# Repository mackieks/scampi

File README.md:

<picture> <source media="(prefers-color-scheme: dark)" srcset="images/logo.png">  </picture> 

Scampi is a truly universal OSHW audio amp for portablizers. Hardware design is tested and working. Firmware is nearly complete.

Features:

- Low-cost 20x20mm 2-layer PCB
- TLV320AIC3110 codec with stereo 1.3W Class-D amps and Class-AB headphone driver
- 5V-tolerant level-shifted I2S input + analog input
- Onboard switching 3.5mm headphone jack
- Solder jumpers for mode selection (15 modes planned)
- Shrimp-themed!🦐

Recommended speakers: [Nintendo Switch 2 speakers](https://www.aliexpress.us/item/3256809887996046.html)

Headphone jack (remove pegs with flush cutters): [PJ320D](https://www.aliexpress.us/item/3256808202284065.html)

Hardware tested and working! Firmware is nearly complete! Supported modes so far:

- [x] Analog input
- [x] SNES
- [x] N64
- [x] GameCube
- [x] Wii
- [x] Wii U
- [ ] PS1
- [ ] PS2
- [ ] PS3
- [x] Saturn
- [x] Dreamcast
- [ ] XBOX
- [ ] Xbox 360
- [ ] Jaguar
- [ ] Neo Geo

## License
Solderpad Hardware License v2.1

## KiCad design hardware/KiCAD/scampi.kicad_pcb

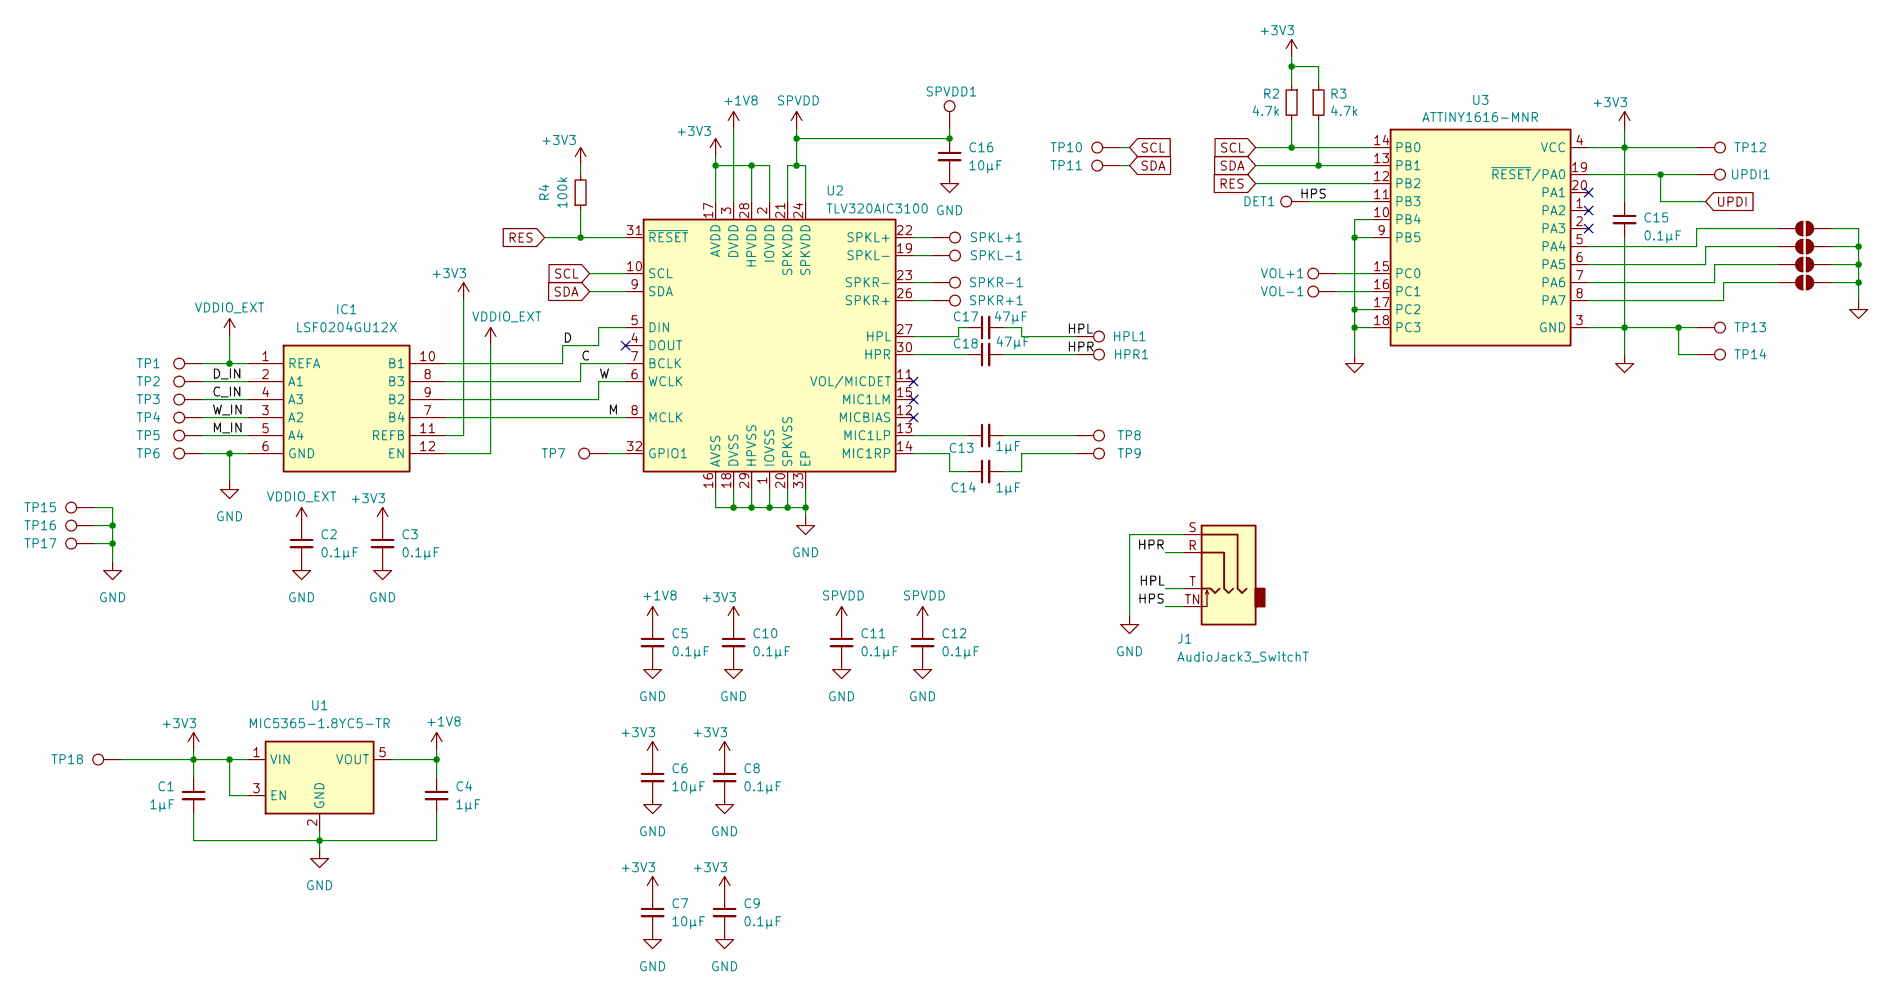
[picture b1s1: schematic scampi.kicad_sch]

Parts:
C1, C4, C13, C14: 1µF; C_0402_1005Metric
C2, C3, C5, C8, C9, C10, C11, C12, C15: 0.1µF; C_0402_1005Metric
C6, C7, C16: 10µF; C_0603_1608Metric
C17, C18: 47µF; C_0603_1608Metric
DET1: pth_pad
HPL1: pth_pad
HPR1: pth_pad
IC1: LSF0204GU12X; Mouser Part Number 771-LSF0204GU12X
J1: AudioJack3_SwitchT; Jack_3.5mm_CUI_SJ-3524-SMT_Horizontal
JP1, JP2, JP3, JP4: SolderJumper_2_Open; small_solder_jumper
R2, R3: 4.7k; R_0402_1005Metric
R4: 100k; R_0402_1005Metric
SPKL+1: pth_pad
SPKL-1: pth_pad
SPKR+1: pth_pad
SPKR-1: pth_pad
SPVDD1: pth_pad
TP1, TP2, TP3, TP4, TP5, TP6, TP8, TP9, TP15, TP16, TP17, TP18: pth_pad
TP7: TestPoint_Pad_D1.0mm
TP10: SCL; TestPoint_Pad_D1.0mm
TP11: SDA; TestPoint_Pad_D1.0mm
TP12: V+; TestPoint_Pad_D1.0mm
TP13: GND; pth_pad
TP14: GND; TestPoint_Pad_D1.0mm
U1: MIC5365-1.8YC5-TR; SOT-353_SC-70-5
U2: TLV320AIC3100; VQFN-32-1EP_5x5mm_P0.5mm_EP3.5x3.5mm
U3: ATTINY1616-MNR; VQFN-20-1EP_3x3mm_P0.4mm_EP1.7x1.7mm
UPDI1: UPDI; TestPoint_Pad_D1.0mm
VOL+1: pth_pad
VOL-1: pth_pad

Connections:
+1V8: C4.1, C5.1, U1.5 (VOUT), U2.3 (DVDD)
+3V3: C1.1, C3.1, C6.1, C7.1, C8.1, C9.1, C10.1, C15.1, IC1.11 (REFB), R2.1, R3.1, R4.2, TP12.1, TP18.1, U1.1 (VIN), U1.3 (EN), U2.2 (IOVDD), U2.17 (AVDD), U2.28 (HPVDD), U3.4 (VCC)
/C: IC1.8 (B3), U2.7 (BCLK)
/C_IN: IC1.4 (A3), TP3.1
/D: IC1.10 (B1), U2.5 (DIN)
/D_IN: IC1.2 (A1), TP2.1
/HPL: C17.2, HPL1.1, J1.T
/HPR: C18.2, HPR1.1, J1.R
/HPS: DET1.1, J1.TN, U3.11 (PB3)
/M: IC1.7 (B4), U2.8 (MCLK)
/M_IN: IC1.5 (A4), TP5.1
/W: IC1.9 (B2), U2.6 (WCLK)
/W_IN: IC1.3 (A2), TP4.1
GND: C1.2, C2.2, C3.2, C4.2, C5.2, C6.2, C7.2, C8.2, C9.2, C10.2, C11.2, C12.2, C15.2, C16.2, IC1.6 (GND), J1.S, JP1.1 (A), JP2.1 (A), JP3.1 (A), JP4.1 (A), TP6.1, TP13.1, TP14.1, TP15.1, TP16.1, TP17.1, U1.2 (GND), U2.1 (IOVSS), U2.16 (AVSS), U2.18 (DVSS), U2.20 (SPKVSS), U2.25 (SPKVSS), U2.29 (HPVSS), U2.33 (EP), U3.3 (GND), U3.9 (PB5), U3.10 (PB4), U3.17 (PC2), U3.18 (PC3), U3.21 (GND)
unnamed: C13.2, TP8.1
unnamed: C14.2, TP9.1
unnamed: JP1.2 (B), U3.5 (PA4)
unnamed: JP2.2 (B), U3.6 (PA5)
unnamed: JP3.2 (B), U3.7 (PA6)
unnamed: JP4.2 (B), U3.8 (PA7)
unnamed: TP7.1, U2.32 (GPIO1)
unnamed: C17.1, U2.27 (HPL)
unnamed: C18.1, U2.30 (HPR)
unnamed: C13.1, U2.13 (MIC1LP)
unnamed: C14.1, U2.14 (MIC1RP)
unnamed: SPKL+1.1, U2.22 (SPKL+)
unnamed: SPKL-1.1, U2.19 (SPKL-)
unnamed: SPKR+1.1, U2.26 (SPKR+)
unnamed: SPKR-1.1, U2.23 (SPKR-)
unnamed: U3.15 (PC0), VOL+1.1
unnamed: U3.16 (PC1), VOL-1.1
RES: R4.1, U2.31 (~RESET), U3.12 (PB2)
SCL: R2.2, TP10.1, U2.10 (SCL), U3.14 (PB0)
SDA: R3.2, TP11.1, U2.9 (SDA), U3.13 (PB1)
SPVDD: C11.1, C12.1, C16.1, SPVDD1.1, U2.21 (SPKVDD), U2.24 (SPKVDD)
UPDI: U3.19 (~RESET/PA0), UPDI1.1
VDDIO_EXT: C2.1, IC1.1 (REFA), IC1.12 (EN), TP1.1

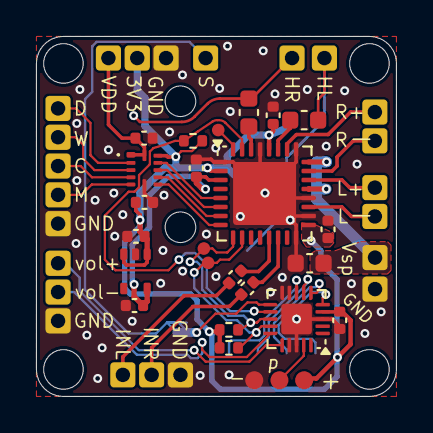
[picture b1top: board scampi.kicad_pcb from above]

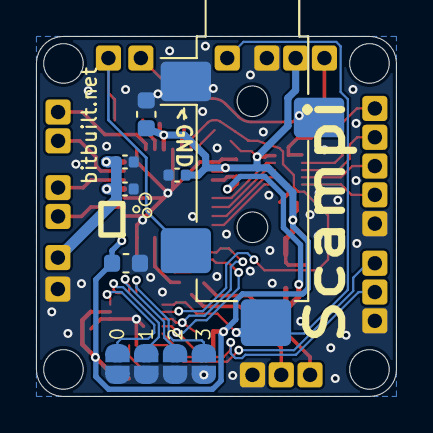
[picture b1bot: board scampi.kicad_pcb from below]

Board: 2 copper layers, 20.0 x 20.0 mm, 59 parts (10 on the bottom side), 37 nets.

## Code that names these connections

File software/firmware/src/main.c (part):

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static volatile uint8_t vol_pot = 0; // analog volume pot reading (0 - 255)

// GPIO pin definitions
static const gpio_t RESET  = {&PORTB, 2}; // PB2
static const gpio_t VOL_UP = {&PORTC, 1}; // PC1
static const gpio_t VOL_DN = {&PORTC, 0}; // PC0
static const gpio_t A_MODE = {&PORTC, 2}; // PC2 (analog vol ctrl mode)

static const gpio_t MODE0 = {&PORTA, 4}; // PA4
static const gpio_t MODE1 = {&PORTA, 5}; // PA5
static const gpio_t MODE2 = {&PORTA, 6}; // PA6
static const gpio_t MODE3 = {&PORTA, 7}; // PA7

// Initialize the RTC for periodic interrupts
void rtc_init()
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
    analog_vol_ctrl = true;

    // ADC1 on VOL_DN (PC0)
    ADC1.CTRLA   = 0x07; // enable ADC in free-running 8-bit mode
    ADC1.CTRLC   = 0x01010011; // reduced capacitance mode, set VREF to VDD, div16 prescaler
    ADC1.MUXPOS  = ADC_MUXPOS_AIN6_gc; // select PC0
    ADC1.COMMAND = 0b1; // start conversion

    gpio_output(VOL_UP); // use VOL_UP to power the volume pot
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
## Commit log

2024-08-30 update logo
2024-08-30 revert logos
2024-08-30 Add gerbers
2024-08-31 add ibom and jig
2024-09-10 board tweaks & firmware
2024-09-10 registers
2024-09-13 Add files via upload
    AIC3110 GPIO1 documentation from E2E
2024-11-05 firmware, new layout
2024-11-05 layout changes, ADC test fw
2024-11-06 finalize layout, add gerbers and step file
2024-11-15 finalize layout!
2024-12-03 add new pic
2024-12-03 firmware work
2024-12-12 Firmware update
2024-12-16 firmware nearly done!
2024-12-16 code cleanup
2024-12-16 update files
2025-02-02 add bom, embed fonts + 3d
2025-02-02 clean up
2025-02-02 remove backups
2025-09-21 Add Gamecube and Wii U modes
2026-03-17 Update main.c
    working on analog volume control
2026-03-19 Update main.c
    flesh out analog volume wheel. add automatic wheel limit calibration
2026-03-19 Update main.c
    Fix headphone detection
2026-03-20 Analog input mode + volume fixes
    - add working analog input mode
    - add switch 2 speaker gain
    - adjusted spk/hp volume in analog and digital input modes
2026-03-25 Add Saturn mode. Add I2S mode details
2026-03-25 Add schematic pdf
2026-03-25 organize schematic and STEP files
2026-03-25 Update schematic
2026-03-25 Update BOM
2026-03-25 update schematic pdf
2026-04-12 add ps1, neo geo modes

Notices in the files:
software/firmware/src/main.c:
MIT License
